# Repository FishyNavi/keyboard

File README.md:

# Hackyboard!
## Overview
They main reason of why this was made is the fact that i play osu. My laptop's keyboard probably doesn't like being smashed at the rate of 12cps so one day i thought that it would be nice to have something to click on.

 I also thought that i should make a keyboard just because i can(and for various other reasons). Routing was kinda time consuming and i tried to minimize the interference between traces. 

I will update this and share the result once i build it!

All of the stuff along with links can be found in `bom.md`

## PCB
`pcb/`
The PCB was designed in KiCAD 10.

- The PCB is designed for Cherry magnetic switches. 
- The sensors' measurement range is ~82.5mT.
- The MCU that's used is STM32G431CBT6

## CASE
`case/`
The case was designed in oneshape.

- Fits with the pcb (wow)
- Looks simple

It's nothing very special actually. Bottom part, pcb and switch plate are sandwiched together and then it is sandwiched again with (another) bottom and top parts of the case. You can see it on the image on top.

All of the parts except the switch plate are designed to be 3d printed. The switch plate should be machined with cnc from 1.5 aluminium plate.

> [!NOTE]
> The switch plate can be cut with lser instead but then you will have to use diffrent kind od screws

About screws, the case should be assembled using M2 screws along with M2 heat inserts. Female to female spacers are required in between pcb and switch plate.
## FIRMWARE
./firmware
The firmware is [libhmk](https://github.com/peppapighs/libhmk)
by peppapighs, which is licensed under GPL-3.0. Changes and additions in
`firmware/` (including the MCU support) will be therefore also
released under GPL-3.0, see `firmware/LICENSE`.
*For now it just is. I didn't test it yet*

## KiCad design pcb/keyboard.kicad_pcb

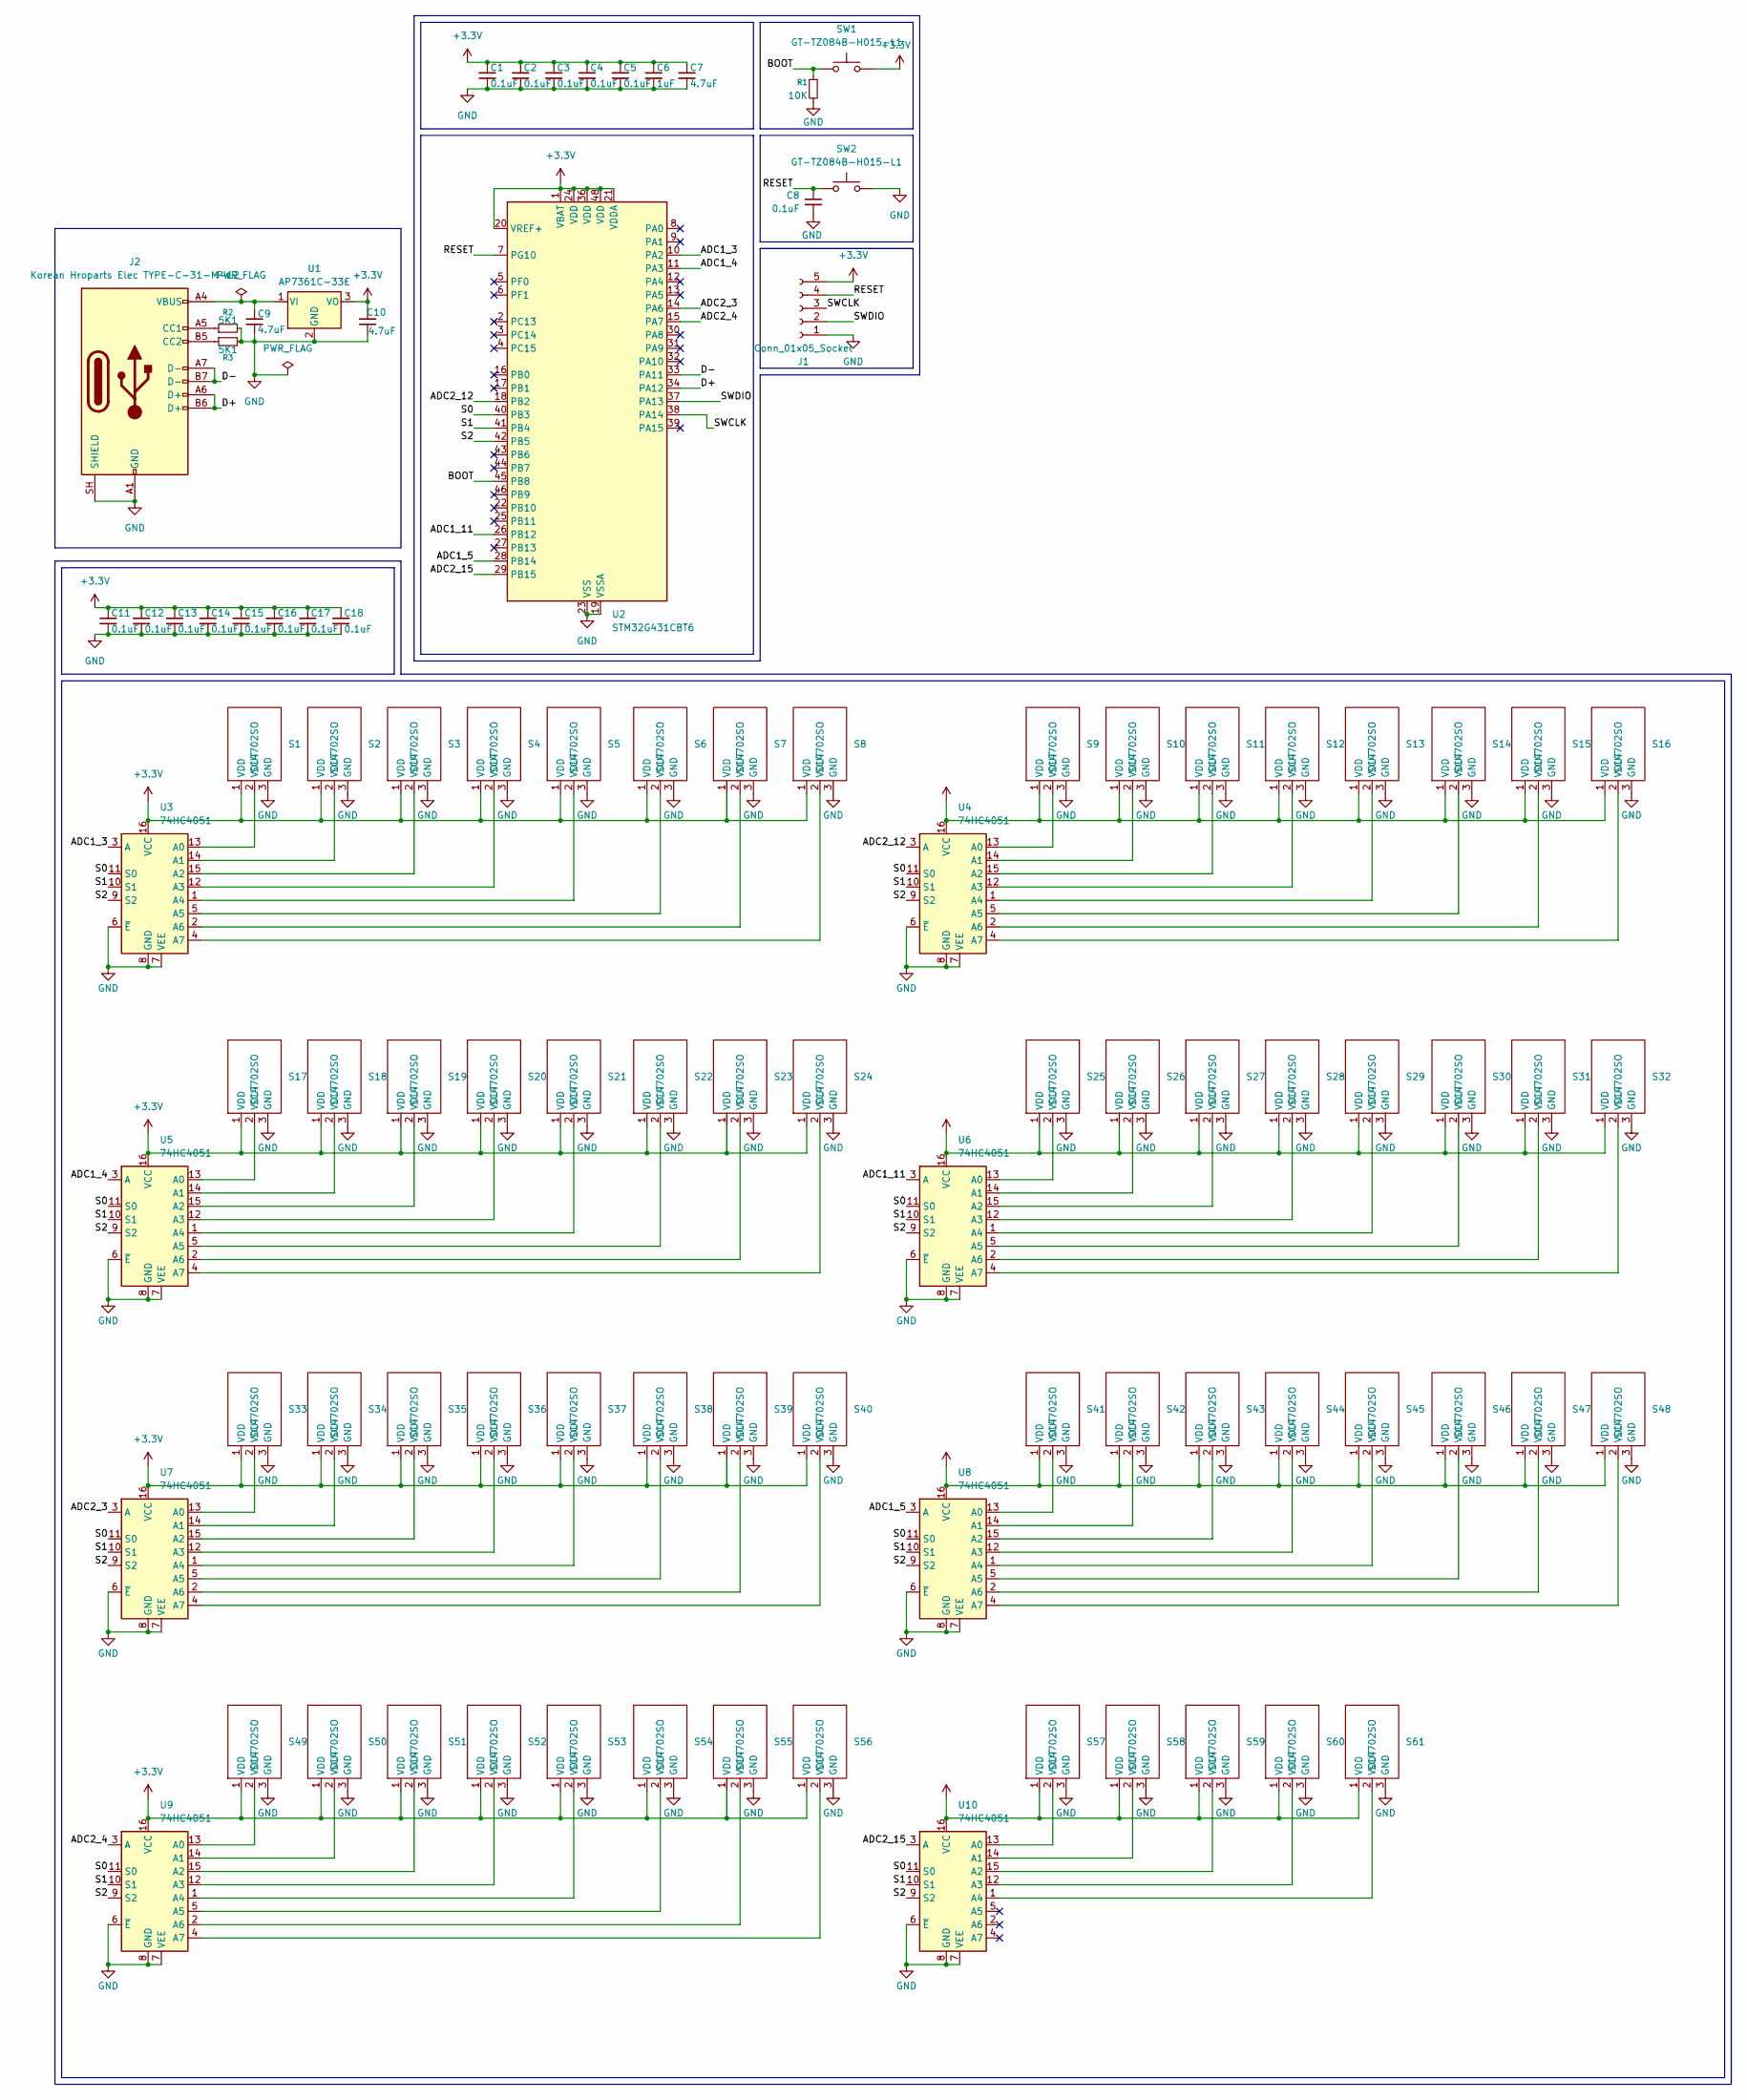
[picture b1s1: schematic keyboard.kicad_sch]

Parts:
C1, C2, C3, C4, C5, C8, C11, C12, C13, C14, C15, C16, C17, C18: 0.1uF; C_0805_2012Metric
C6: 1uF; C_0805_2012Metric
C7, C9, C10: 4.7uF; C_0805_2012Metric
J1: Conn_01x05_Socket; SolderWire-1sqmm_1x05_P5.4mm_D1.4mm_OD2.7mm
J2: Korean Hroparts Elec TYPE-C-31-M-12; USB_C_Receptacle_G-Switch_GT-USB-7010ASV
R1: 10K; R_0805_2012Metric
R2, R3: 5K1; R_0805_2012Metric
S1, S2, S3, S4, S5, S6, S7, S8, S9, S10, S11, S12, S13, S14, S15, S16, S17, S18, S19, S20, S21, S22, S23, S24, S25, S26, S27, S28, S29, S30, S31, S32, S33, S34, S35, S36, S37, S38, S39, S40, S41, S42, S43, S44, S45, S46, S47, S48, S49, S50, S51, S52, S53, S54, S55, S56, S57, S58, S59, S60, S61: SC4702SO; SOT-23-3_HE_SENSOR
SW1, SW2: GT-TZ084B-H015-L1; SMD-4P,5.2x5.2mm
U1: AP7361C-33E; SOT-223-3_TabPin2
U2: STM32G431CBT6; LQFP-48_7x7mm_P0.5mm
U3, U4, U5, U6, U7, U8, U9, U10: 74HC4051; TSSOP-16_4.4x5mm_P0.65mm

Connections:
+3.3V: C1.1, C2.1, C3.1, C4.1, C5.1, C6.1, C7.1, C10.1, C11.1, C12.1, C13.1, C14.1, C15.1, C16.1, C17.1, C18.1, J1.5, S1.1 (VDD), S2.1 (VDD), S3.1 (VDD), S4.1 (VDD), S5.1 (VDD), S6.1 (VDD), S7.1 (VDD), S8.1 (VDD), S9.1 (VDD), S10.1 (VDD), S11.1 (VDD), S12.1 (VDD), S13.1 (VDD), S14.1 (VDD), S15.1 (VDD), S16.1 (VDD), S17.1 (VDD), S18.1 (VDD), S19.1 (VDD), S20.1 (VDD), S21.1 (VDD), S22.1 (VDD), S23.1 (VDD), S24.1 (VDD), S25.1 (VDD), S26.1 (VDD), S27.1 (VDD), S28.1 (VDD), S29.1 (VDD), S30.1 (VDD), S31.1 (VDD), S32.1 (VDD), S33.1 (VDD), S34.1 (VDD), S35.1 (VDD), S36.1 (VDD), S37.1 (VDD), S38.1 (VDD), S39.1 (VDD), S40.1 (VDD), S41.1 (VDD), S42.1 (VDD), S43.1 (VDD), S44.1 (VDD), S45.1 (VDD), S46.1 (VDD), S47.1 (VDD), S48.1 (VDD), S49.1 (VDD), S50.1 (VDD), S51.1 (VDD), S52.1 (VDD), S53.1 (VDD), S54.1 (VDD), S55.1 (VDD), S56.1 (VDD), S57.1 (VDD), S58.1 (VDD), S59.1 (VDD), S60.1 (VDD), S61.1 (VDD), SW1.1, U1.3 (VO), U2.1 (VBAT), U2.20 (VREF+), U2.21 (VDDA), U2.24 (VDD), U2.36 (VDD), U2.48 (VDD), U3.16 (VCC), U4.16 (VCC), U5.16 (VCC), U6.16 (VCC), U7.16 (VCC), U8.16 (VCC), U9.16 (VCC), U10.16 (VCC)
/ADC1_3: U2.10 (PA2), U3.3 (A)
/ADC1_4: U2.11 (PA3), U5.3 (A)
/ADC1_5: U2.28 (PB14), U8.3 (A)
/ADC1_11: U2.26 (PB12), U6.3 (A)
/ADC2_3: U2.14 (PA6), U7.3 (A)
/ADC2_4: U2.15 (PA7), U9.3 (A)
/ADC2_12: U2.18 (PB2), U4.3 (A)
/ADC2_15: U2.29 (PB15), U10.3 (A)
/BOOT: R1.1, SW1.2, U2.45 (PB8)
/D+: J2.A6 (D+), J2.B6 (D+), U2.34 (PA12)
/D-: J2.A7 (D-), J2.B7 (D-), U2.33 (PA11)
/RESET: C8.1, J1.4, SW2.2, U2.7 (PG10)
/S0: U2.40 (PB3), U3.11 (S0), U4.11 (S0), U5.11 (S0), U6.11 (S0), U7.11 (S0), U8.11 (S0), U9.11 (S0), U10.11 (S0)
/S1: U2.41 (PB4), U3.10 (S1), U4.10 (S1), U5.10 (S1), U6.10 (S1), U7.10 (S1), U8.10 (S1), U9.10 (S1), U10.10 (S1)
/S2: U2.42 (PB5), U3.9 (S2), U4.9 (S2), U5.9 (S2), U6.9 (S2), U7.9 (S2), U8.9 (S2), U9.9 (S2), U10.9 (S2)
/SWCLK: J1.3, U2.38 (PA14)
/SWDIO: J1.2, U2.37 (PA13)
GND: C1.2, C2.2, C3.2, C4.2, C5.2, C6.2, C7.2, C8.2, C9.2, C10.2, C11.2, C12.2, C13.2, C14.2, C15.2, C16.2, C17.2, C18.2, J1.1, J2.A1 (GND), J2.A12 (GND), J2.B1 (GND), J2.B12 (GND), J2.SH (SHIELD), R1.2, R2.2, R3.2, S1.3 (GND), S2.3 (GND), S3.3 (GND), S4.3 (GND), S5.3 (GND), S6.3 (GND), S7.3 (GND), S8.3 (GND), S9.3 (GND), S10.3 (GND), S11.3 (GND), S12.3 (GND), S13.3 (GND), S14.3 (GND), S15.3 (GND), S16.3 (GND), S17.3 (GND), S18.3 (GND), S19.3 (GND), S20.3 (GND), S21.3 (GND), S22.3 (GND), S23.3 (GND), S24.3 (GND), S25.3 (GND), S26.3 (GND), S27.3 (GND), S28.3 (GND), S29.3 (GND), S30.3 (GND), S31.3 (GND), S32.3 (GND), S33.3 (GND), S34.3 (GND), S35.3 (GND), S36.3 (GND), S37.3 (GND), S38.3 (GND), S39.3 (GND), S40.3 (GND), S41.3 (GND), S42.3 (GND), S43.3 (GND), S44.3 (GND), S45.3 (GND), S46.3 (GND), S47.3 (GND), S48.3 (GND), S49.3 (GND), S50.3 (GND), S51.3 (GND), S52.3 (GND), S53.3 (GND), S54.3 (GND), S55.3 (GND), S56.3 (GND), S57.3 (GND), S58.3 (GND), S59.3 (GND), S60.3 (GND), S61.3 (GND), SW2.1, U1.2 (GND), U2.19 (VSSA), U2.23 (VSS), U2.35 (VSS), U2.47 (VSS), U3.6 (~E), U3.7 (VEE), U3.8 (GND), U4.6 (~E), U4.7 (VEE), U4.8 (GND), U5.6 (~E), U5.7 (VEE), U5.8 (GND), U6.6 (~E), U6.7 (VEE), U6.8 (GND), U7.6 (~E), U7.7 (VEE), U7.8 (GND), U8.6 (~E), U8.7 (VEE), U8.8 (GND), U9.6 (~E), U9.7 (VEE), U9.8 (GND), U10.6 (~E), U10.7 (VEE), U10.8 (GND)
unnamed: J2.A5 (CC1), R2.1
unnamed: J2.B5 (CC2), R3.1
unnamed: S1.2 (VOUT), U3.13 (A0)
unnamed: S2.2 (VOUT), U3.14 (A1)
unnamed: S3.2 (VOUT), U3.15 (A2)
unnamed: S4.2 (VOUT), U3.12 (A3)
unnamed: S5.2 (VOUT), U3.1 (A4)
unnamed: S6.2 (VOUT), U3.5 (A5)
unnamed: S7.2 (VOUT), U3.2 (A6)
unnamed: S8.2 (VOUT), U3.4 (A7)
unnamed: S9.2 (VOUT), U4.13 (A0)
unnamed: S10.2 (VOUT), U4.14 (A1)
unnamed: S11.2 (VOUT), U4.15 (A2)
unnamed: S12.2 (VOUT), U4.12 (A3)
unnamed: S13.2 (VOUT), U4.1 (A4)
unnamed: S14.2 (VOUT), U4.5 (A5)
unnamed: S15.2 (VOUT), U4.2 (A6)
unnamed: S16.2 (VOUT), U4.4 (A7)
unnamed: S17.2 (VOUT), U5.13 (A0)
unnamed: S18.2 (VOUT), U5.14 (A1)
unnamed: S19.2 (VOUT), U5.15 (A2)
unnamed: S20.2 (VOUT), U5.12 (A3)
unnamed: S21.2 (VOUT), U5.1 (A4)
unnamed: S22.2 (VOUT), U5.5 (A5)
unnamed: S23.2 (VOUT), U5.2 (A6)
unnamed: S24.2 (VOUT), U5.4 (A7)
unnamed: S25.2 (VOUT), U6.13 (A0)
unnamed: S26.2 (VOUT), U6.14 (A1)
unnamed: S27.2 (VOUT), U6.15 (A2)
unnamed: S28.2 (VOUT), U6.12 (A3)
unnamed: S29.2 (VOUT), U6.1 (A4)
unnamed: S30.2 (VOUT), U6.5 (A5)
unnamed: S31.2 (VOUT), U6.2 (A6)
unnamed: S32.2 (VOUT), U6.4 (A7)
unnamed: S33.2 (VOUT), U7.13 (A0)
unnamed: S34.2 (VOUT), U7.14 (A1)
unnamed: S35.2 (VOUT), U7.15 (A2)
unnamed: S36.2 (VOUT), U7.12 (A3)
unnamed: S37.2 (VOUT), U7.1 (A4)
unnamed: S38.2 (VOUT), U7.5 (A5)
unnamed: S39.2 (VOUT), U7.2 (A6)
unnamed: S40.2 (VOUT), U7.4 (A7)
unnamed: S41.2 (VOUT), U8.13 (A0)
unnamed: S42.2 (VOUT), U8.14 (A1)
unnamed: S43.2 (VOUT), U8.15 (A2)
unnamed: S44.2 (VOUT), U8.12 (A3)
unnamed: S45.2 (VOUT), U8.1 (A4)
unnamed: S46.2 (VOUT), U8.5 (A5)
unnamed: S47.2 (VOUT), U8.2 (A6)
unnamed: S48.2 (VOUT), U8.4 (A7)
unnamed: S49.2 (VOUT), U9.13 (A0)
unnamed: S50.2 (VOUT), U9.14 (A1)
unnamed: S51.2 (VOUT), U9.15 (A2)
unnamed: S52.2 (VOUT), U9.12 (A3)
unnamed: S53.2 (VOUT), U9.1 (A4)
unnamed: S54.2 (VOUT), U9.5 (A5)
unnamed: S55.2 (VOUT), U9.2 (A6)
unnamed: S56.2 (VOUT), U9.4 (A7)
unnamed: S57.2 (VOUT), U10.13 (A0)
unnamed: S58.2 (VOUT), U10.14 (A1)
unnamed: S59.2 (VOUT), U10.15 (A2)
unnamed: S60.2 (VOUT), U10.12 (A3)
unnamed: S61.2 (VOUT), U10.1 (A4)
unnamed: C9.1, J2.A4 (VBUS), J2.A9 (VBUS), J2.B4 (VBUS), J2.B9 (VBUS), U1.1 (VI)

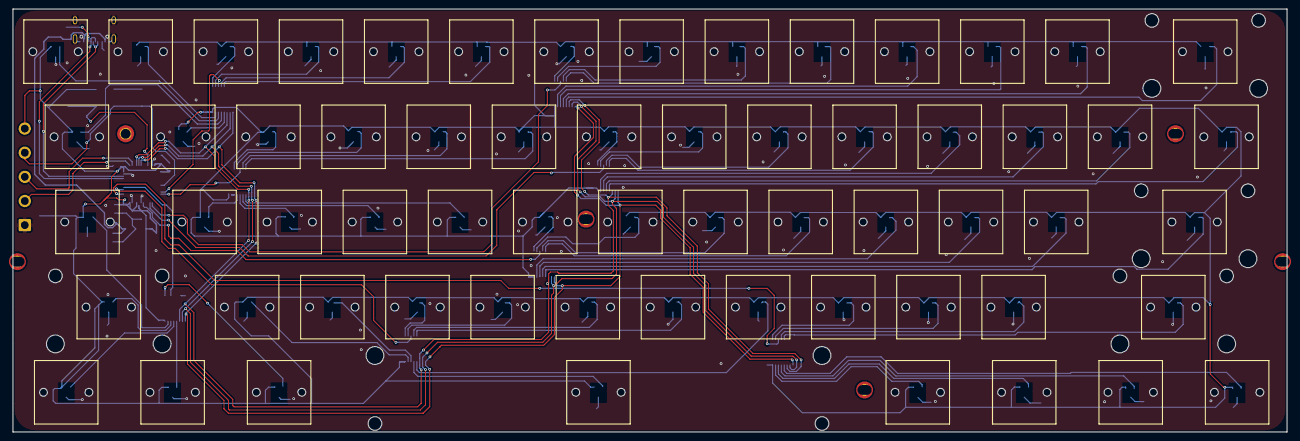
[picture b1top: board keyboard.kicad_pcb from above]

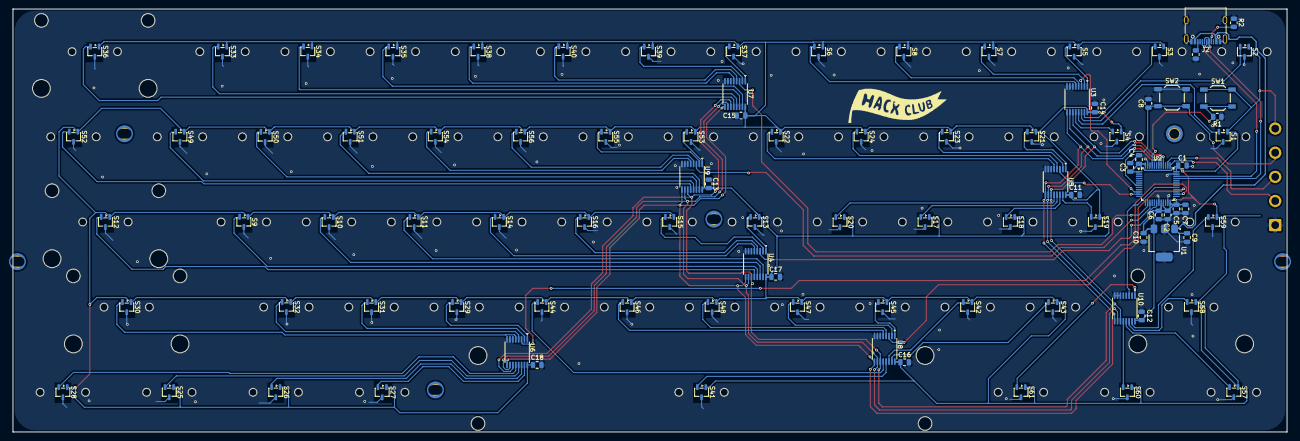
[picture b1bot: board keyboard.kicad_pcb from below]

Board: 2 copper layers, 285.0 x 94.6 mm, 157 parts (96 on the bottom side), 83 nets.

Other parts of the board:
REF1, REF2, REF3, REF4, REF5, REF6, REF7, REF8, REF9, REF10, REF11, REF12, REF13, REF16, REF17, REF18, REF19, REF20, REF21, REF22, REF23, REF24, REF25, REF26, REF27, REF30, REF31, REF32, REF33, REF34, REF35, REF36, REF37, REF38, REF39, REF40, REF43, REF44, REF45, REF46, REF47, REF48, REF49, REF50, REF51, REF52: SW_Cherry_MX_PCB_1.00u_no_pins
REF14: SW_Cherry_MX_PCB_2.00u_no_pins
REF15, REF28: SW_Cherry_MX_PCB_1.50u_no_pins
REF29: SW_Cherry_MX_PCB_1.75u_no_pins
REF41, REF42: SW_Cherry_MX_PCB_2.25u_no_pins
REF53: SW_Cherry_MX_PCB_2.75u_no_pins
REF54, REF55, REF56, REF58, REF59, REF60, REF61: SW_Cherry_MX_PCB_1.25u_no_pins
REF57: SW_Cherry_MX_PCB_6.25u_no_pins

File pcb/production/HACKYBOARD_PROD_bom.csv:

Designator,Footprint,Quantity,Value,LCSC Part #
"C1, C11, C12, C13, C14, C15, C16, C17, C18, C2, C3, C4, C5, C8",0805,14,0.1uF,
"C10, C7, C9",0805,3,4.7uF,
C6,0805,1,1uF,
J1,SolderWire-1sqmm_1x05_P5.4mm_D1.4mm_OD2.7mm,1,Conn_01x05_Socket,
J2,USB_C_Receptacle_G-Switch_GT-USB-7010ASV,1,Korean Hroparts Elec TYPE-C-31-M-12,
R1,0805,1,10K,
"R2, R3",0805,2,5K1,
"REF1, REF10, REF11, REF12, REF13, REF16, REF17, REF18, REF19, REF2, REF20, REF21, REF22, REF23, REF24, REF25, REF26, REF27, REF3, REF30, REF31, REF32, REF33, REF34, REF35, REF36, REF37, REF38, REF39, REF4, REF40, REF43, REF44, REF45, REF46, REF47, REF48, REF49, REF5, REF50, REF51, REF52, REF6, REF7, REF8, REF9",SW_Cherry_MX_PCB_1.00u_no_pins,46,SW_Cherry_MX_PCB_1.00u_no_pins,
REF14,SW_Cherry_MX_PCB_2.00u_no_pins,1,SW_Cherry_MX_PCB_2.00u_no_pins,
"REF15, REF28",SW_Cherry_MX_PCB_1.50u_no_pins,2,SW_Cherry_MX_PCB_1.50u_no_pins,
REF29,SW_Cherry_MX_PCB_1.75u_no_pins,1,SW_Cherry_MX_PCB_1.75u_no_pins,
"REF41, REF42",SW_Cherry_MX_PCB_2.25u_no_pins,2,SW_Cherry_MX_PCB_2.25u_no_pins,
REF53,SW_Cherry_MX_PCB_2.75u_no_pins,1,SW_Cherry_MX_PCB_2.75u_no_pins,
"REF54, REF55, REF56, REF58, REF59, REF60, REF61",SW_Cherry_MX_PCB_1.25u_no_pins,7,SW_Cherry_MX_PCB_1.25u_no_pins,
REF57,SW_Cherry_MX_PCB_6.25u_no_pins,1,SW_Cherry_MX_PCB_6.25u_no_pins,
"S1, S10, S11, S12, S13, S14, S15, S16, S17, S18, S19, S2, S20, S21, S22, S23, S24, S25, S26, S27, S28, S29, S3, S30, S31, S32, S33, S34, S35, S36, S37, S38, S39, S4, S40, S41, S42, S43, S44, S45, S46, S47, S48, S49, S5, S50, S51, S52, S53, S54, S55, S56, S57, S58, S59, S6, S60, S61, S7, S8, S9",SOT-23-3_HE_SENSOR,61,SC4702SO,
"SW1, SW2",SW_SPST_TL3342,2,GT-TZ084B-H015-L1,
U1,SOT-223-3_TabPin2,1,AP7361C-33E,
"U10, U3, U4, U5, U6, U7, U8, U9",TSSOP-16_4.4x5mm_P0.65mm,8,74HC4051,
U2,LQFP-48_7x7mm_P0.5mm,1,STM32G431CBT6,
